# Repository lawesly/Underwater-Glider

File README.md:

# Underwater-Glider
Projeto de concepção e construção de um glider subaquático de baixo custo

# Resumo

Este projeto aborda o estudo de veículos subaquáticos de navegação autônoma, sendo seu foco principal a modelagem e construção de um protótipo do tipo Glider. Este robô pode ser definido como um veículo planador subaquático de baixo gasto energético que se locomove somente com a alteração de  seu peso e movimentação do centro de massa. Através deste trabalho foi realizando um estudo dos principais modelos existentes assim como suas principais características de funcionamento. Após este estudo foram pesquisadas técnicas para concepção do protótipo funcional junto de sua instrumentação básica. A conclusão de toda esta metodologia foi a construção de um glider, em escala simplificada, desenvolvido totalmente através do uso de técnicas e materiais de baixo custo que será compartilhado de forma gratuita com a comunidade de acadêmica. Com base nestes resultados, foi possível identificar os pontos de melhoria que serão aplicados em próximas versões, tornando o protótipo um produto confiável, de fácil reprodução e que poderá ser utilizado para estudos de controle e sensoriamento subaquático de maneira simples e acessível.

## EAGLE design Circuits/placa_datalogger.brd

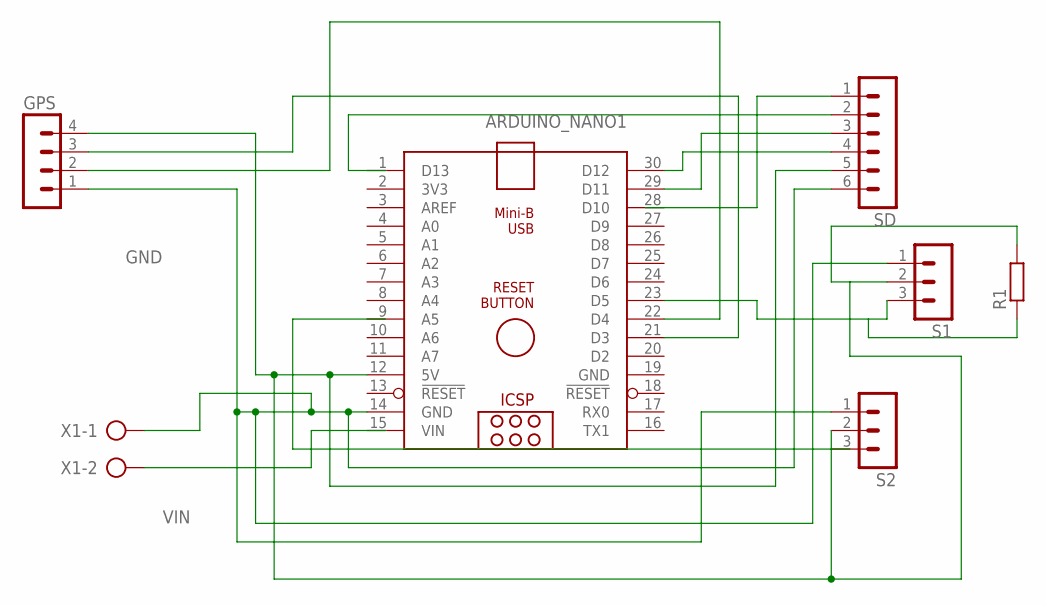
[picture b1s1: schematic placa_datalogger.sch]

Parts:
ARDUINO_NANO1: ARDUINO_NANO
GPS: MA04-1
R1: R-EU_0204/7; 0204/7
S1, S2: MA03-1
SD: MA06-1
X1: AK500/2-H

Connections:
5V: ARDUINO_NANO1.12 (5V), GPS.4, R1.2, S1.2, S2.2, SD.5
GND: ARDUINO_NANO1.14 (GND), ARDUINO_NANO1.19 (GND), GPS.1, S1.1, S2.1, SD.6, X1.1
unnamed: ARDUINO_NANO1.21 (D3), GPS.3
unnamed: ARDUINO_NANO1.22 (D4), GPS.2
unnamed: ARDUINO_NANO1.28 (D10), SD.1
unnamed: ARDUINO_NANO1.29 (D11), SD.3
unnamed: ARDUINO_NANO1.30 (D12), SD.4
unnamed: ARDUINO_NANO1.23 (D5), R1.1, S1.3
VIN: ARDUINO_NANO1.15 (VIN), X1.2

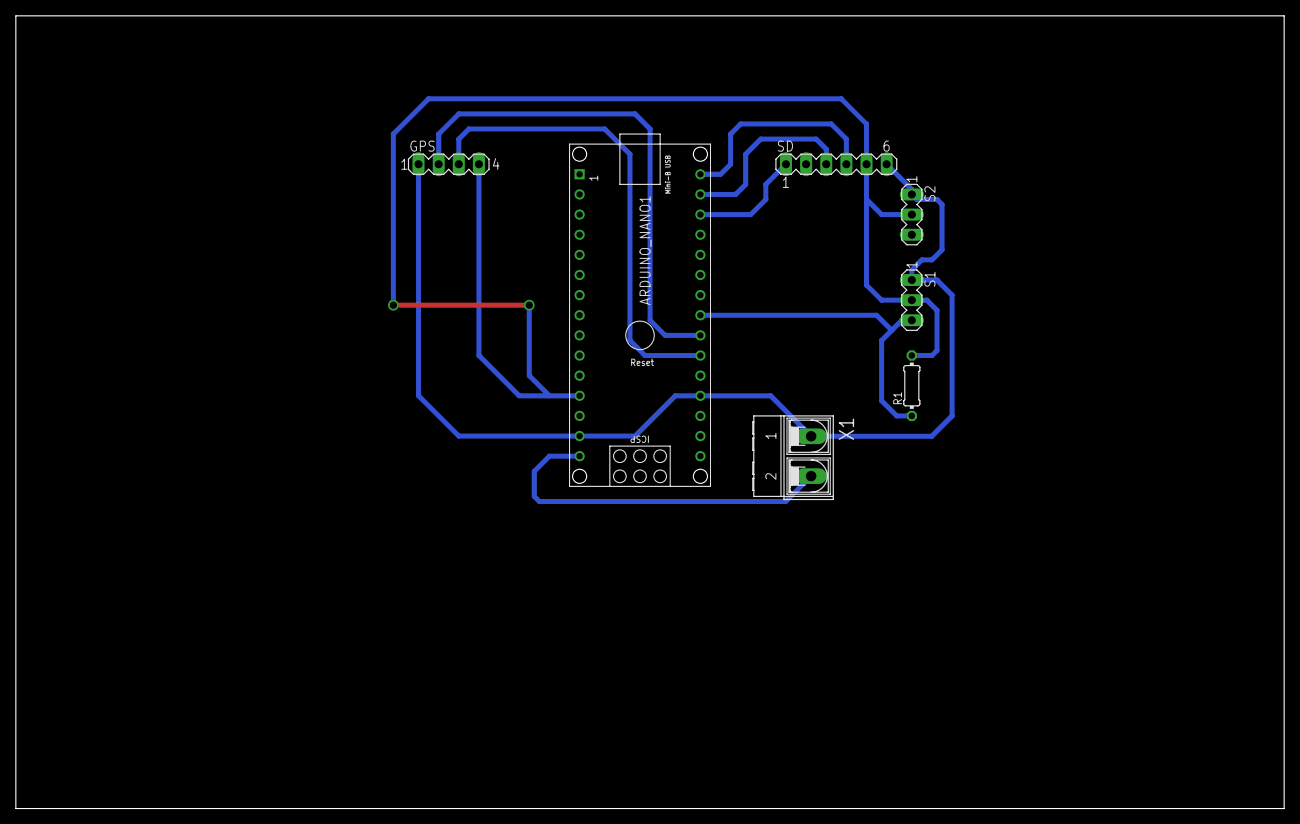
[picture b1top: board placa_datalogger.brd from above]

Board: 2 copper layers, 160.0 x 100.0 mm, 7 parts (0 on the bottom side), 9 nets.

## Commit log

2019-04-14 Adição dos arquivos iniciais
    Códigos base, circuitos fotos
2019-04-14 Add dos arquivos de modelagem 3D
    Arquivos stl utilizados para a fabricação das peças
2019-04-14 Add do código de locomoção básico
2019-04-14 Add código glider completo
2019-04-14 Descrição Read.me
2019-04-14 Atualização read.me
2019-04-14 Adição de fotos
